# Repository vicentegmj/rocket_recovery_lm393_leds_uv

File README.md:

# rocket_recovery_lm393_leds_uv

Sistema eletrônico cuja funcionalidade prevista é liberar um paraquedas logo após atingir o apogeu da trajetória do lançamento. O funcionamento do cirtuto é basedo no monitoramento de tensões elétricas em duas portas analógicas do CI LM393, as tensões são geradas por 2 LEDs UV. LED UV tem a paricularidade de criar uma tensão V nos seus terminais quando exposta á luz ultravioleta, no caso do foguete, a luz ultravioleta do Sol. Quando há inversão da tensão nos terminais o LM393 atravéz do seu pino de saída faz a saturação do TIP122 que passa a conduzir corrente elétrica direta da bateria de 9V fazendo a ignição da carga.

Esquema elétrico 25-06-2025

Placa de circuito 25-06-2025

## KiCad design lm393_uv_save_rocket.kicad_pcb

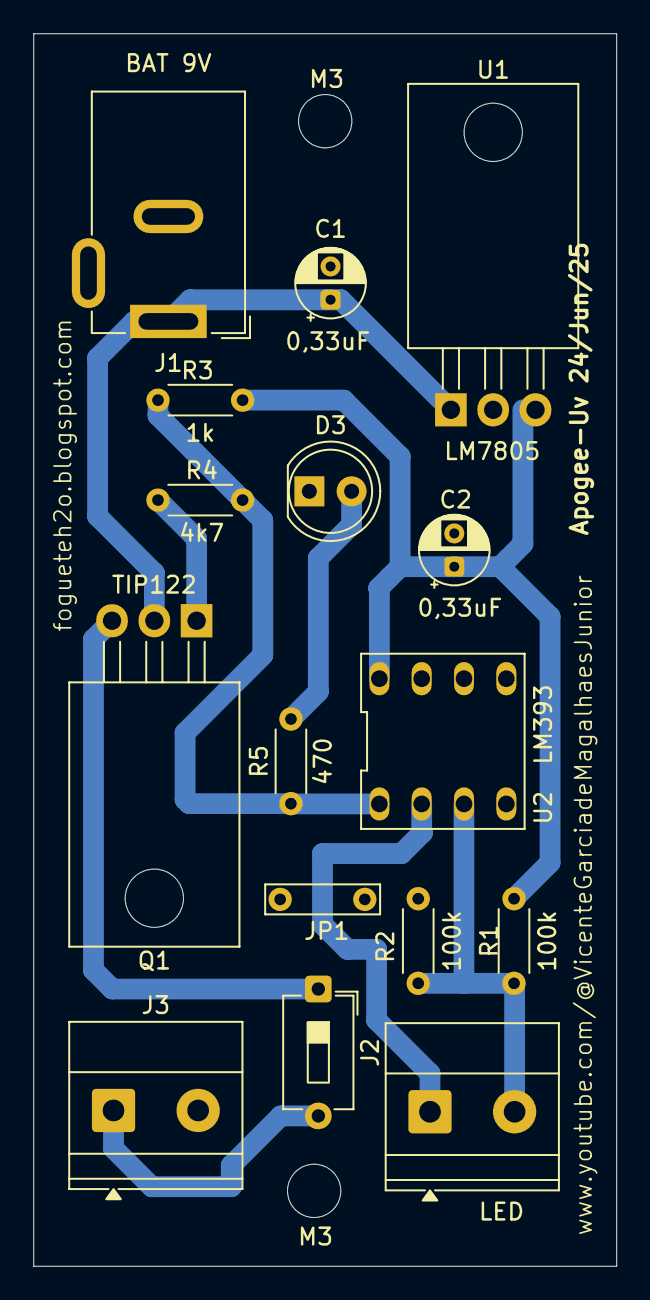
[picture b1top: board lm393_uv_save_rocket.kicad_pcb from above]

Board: 2 copper layers, 35.0 x 74.0 mm, 18 parts (0 on the bottom side), 10 nets.

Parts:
C1, C2: 0,33uF; CP_Radial_D4.0mm_P2.00mm
D2: LED; TerminalBlock_Phoenix_MKDS-1,5-2-5.08_1x02_P5.08mm_Horizont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
D3: LED; LED_D5.0mm
J1: BAT 9V; BarrelJack_GCT_DCJ200-10-A_Horizontal
J2: JUMP; SW_DIP_SPSTx01_Slide_6.7x4.1mm_W7.62mm_P2.54mm_LowProfile
J3: IGNITER; TerminalBlock_Phoenix_MKDS-1,5-2-5.08_1x02_P5.08mm_Horizont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
JP1: Jumper_2_Bridged; TestPoint_Bridge_Pitch5.08mm_Drill0.7mm
M3, M3#2: M3; MountingHole_3.2mm_M3
Q1: TIP122; TO-220-3_Horizontal_TabDown
R1, R2: 100k; R_Axial_DIN0204_L3.6mm_D1.6mm_P5.08mm_Horizontal
R3: 1k; R_Axial_DIN0204_L3.6mm_D1.6mm_P5.08mm_Horizontal
R4: 4k7; R_Axial_DIN0204_L3.6mm_D1.6mm_P5.08mm_Horizontal
R5: 470; R_Axial_DIN0204_L3.6mm_D1.6mm_P5.08mm_Horizontal
U1: LM7805; TO-220-3_Horizontal_TabDown
U2: LM393; DIP-8_296_ELL

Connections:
/GND: C1.2, C2.2, D3.1 (K), J1.2, J3.2, JP1.1 (A), R2.1, U1.2 (GND), U2.4 (GND)
/VCC: C2.1, R1.1, R3.1, U1.3 (VO), U2.8 (VCC)
unnamed: D2.2 (A), R1.2, R2.2, U2.3 (+)
unnamed: D2.1 (K), U2.2 (-)
unnamed: D3.2 (A), R5.2
unnamed: C1.1, J1.1, Q1.2 (C), U1.1 (VI)
unnamed: J2.1, Q1.3 (E)
unnamed: J2.2, J3.1
unnamed: Q1.1 (B), R4.2
unnamed: R3.2, R4.1, R5.1, U2.1

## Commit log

2025-06-25 Primeiro push de arquivos
2025-06-25 Atalização do README
2025-06-25 Ajuste trilhas placa
2025-06-26 Novo led que informa posição correta dos led UV, e funcionamento do circuito
2025-06-26 Arquivo txt de simulação no falstad.com
2025-06-26 Alteração do tipo do conector da bat 9v
2025-06-26 Ajustes de posicionamento de componentes na placa
2025-06-27 update de backup
2025-06-27 jumper de segurança
2025-06-27 basicamente update de backup
